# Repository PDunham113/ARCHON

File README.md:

# ARCHON
**A**ddressable **R**GB LED **CON**troller *(The **'h'** is nonexistent)*

The ultimate goal is to control an arbitrary number of addressable (WS2812 or
similar) from an ATMega328p, with a robust serial protocol to communicate to a
IoT-friendly mainboard (Raspberry Pi Zero W or similar).

Current state is somewhat less than that (setting up tools, etc.)

## Folders

### hardware (v0.0.0)
Contains EAGLE files for the ARCHON controller board

### software (v0.0.0)
Contains firmware for ARCHON

## Setup
Working with the hardware requires an installation of Autodesk EAGLE (v8.5.2 or
later), as well as a copy of Sparkfun's EAGLE library. Installation is left up
to the user.

Working with the software requires a number of (non-Windows-friendly) tools. To
automate the installation process and facilitate the ability to work on
multiple projects at once, a Vagrantfile is maintained with all the required
tools and dependencies.

### Installing Vagrant
You will need:
-   Vagrant [(HashiCorp)][vagrant_install]
-   VirtualBox [(Oracle)][virtualbox_install]
    -   Other VMs are available, but not actively supported by this project
-   VirtualBox Extensions [(Same place)][virtualbox_install]

The Vagrantfile used here is split into 3 parts.
-   `Vagrantfile`
    -   Deals with general configuration of VM instance
-   `Vagrantfile.project`
    -   Deals with project-specific tools and dependencies
-   `Vagrantfile.local`
    -   Deals with user preferences and machine-specific settings. As this is
        user-specific, Git will ignore this. A template
        (`Vagrantfile.local.example`) is included. Rename and enjoy!

To boot the VM, navigate to the project folder and run the following commands:
```
vagrant up
vagrant ssh
```

#### Common Errors
-   Ensure that virtualization extensions are enabled (you may need to check
    your BIOS)

[vagrant_install]: https://www.vagrantup.com/downloads.html
[virtualbox_install]: https://www.virtualbox.org/wiki/Downloads

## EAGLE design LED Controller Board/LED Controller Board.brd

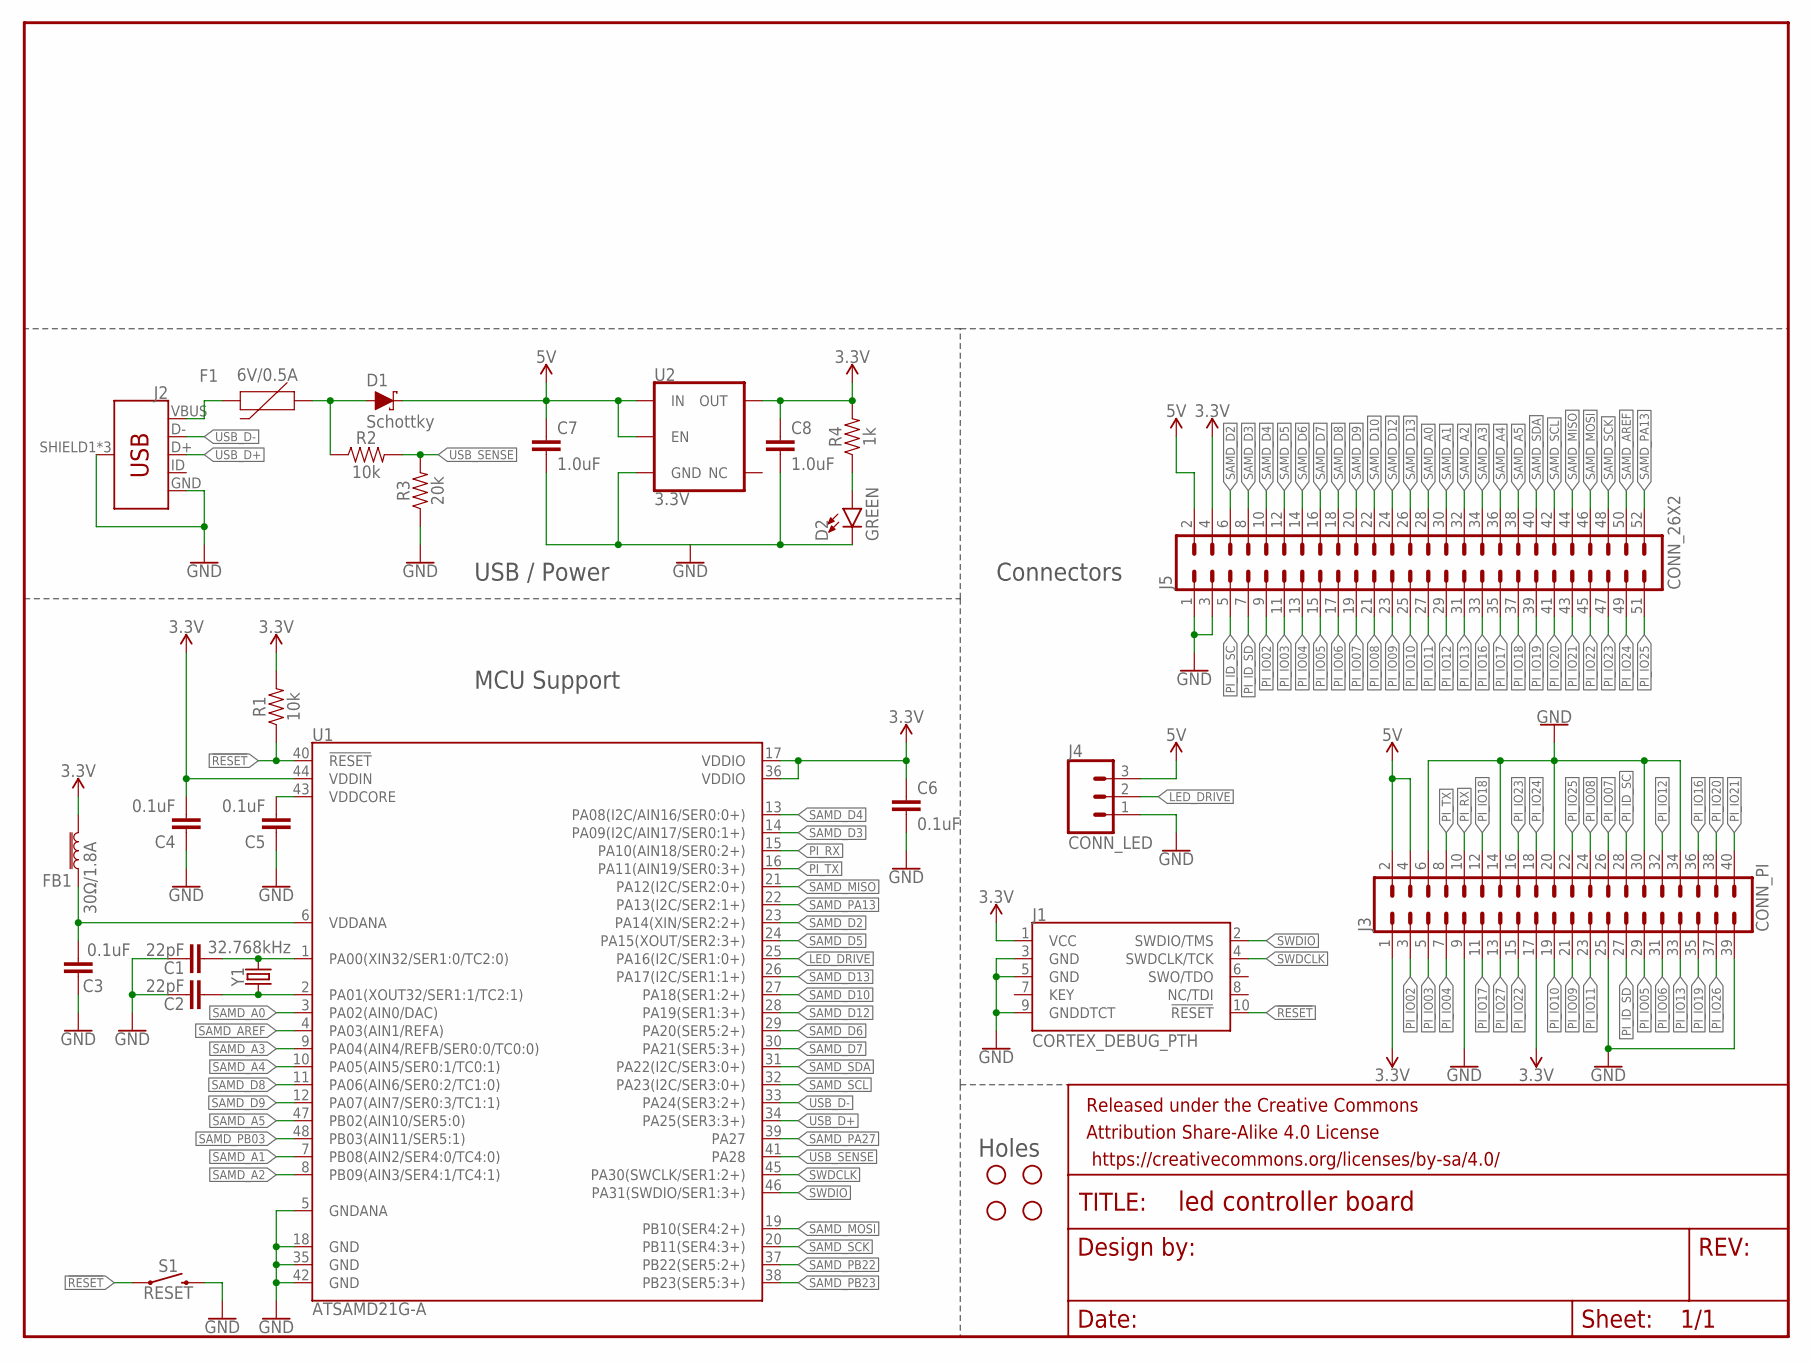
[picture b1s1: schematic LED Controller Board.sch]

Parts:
C1, C2: 22pF; 0603
C3, C4, C5, C6: 0.1uF; 0603
C7, C8: 1.0uF; 0603
D1: Schottky; SOD-323
D2: GREEN; LED-0603
F1: 6V/0.5A; 1206
FB1: 30Ω/1.8A; 0603
FRAME1: FRAME-LETTERNO_PACKAGE; DUMMY
H1, H2, H3, H4: STAND-OFFTIGHT; STAND-OFF-TIGHT
J1: CORTEX_DEBUG_PTH; 2X5-PTH-1.27MM
J2: USB_MICRO-B_FEMALE-SMT; USB-B-MICRO-SMD
J3: CONN_PI; 2X20
J4: CONN_LED; 1X03_LOCK
J5: CONN_26X2; 2X26
R1, R2: 10k; 0603
R3: 20k; 0603
R4: 1k; 0603
S1: RESET; TACTILE_SWITCH_PTH_RIGHT_ANGLE_KIT
U1: ATSAMD21G-A; TQFP-48
U2: 3.3V; SOT23-5
Y1: 32.768kHz; CRYSTAL-SMD-3.2X1.5MM

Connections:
3.3V: C4.2, C6.1, C8.1, FB1.2, J1.1 (VCC), J3.1, J3.17, J5.4, R1.2, R4.2, U1.17 (VDDIO), U1.36 (VDDIO), U1.44 (VDDIN), U2.5 (OUT)
5V: C7.1, D1.C, J3.2, J3.4, J4.3, J5.2, U2.1 (IN), U2.3 (EN)
!RESET: J1.10 (!RESET), R1.1, S1.1, U1.40 (!RESET!)
GND: C1.1, C2.1, C3.1, C4.1, C5.1, C6.2, C7.2, C8.2, D2.C, J1.3 (GND), J1.5 (GND), J1.9 (GNDDTCT), J2.GND, J2.SHIELD1 (SHIELD), J2.SHIELD2 (SHIELD), J2.SHIELD3 (SHIELD), J3.6, J3.9, J3.14, J3.20, J3.25, J3.30, J3.34, J3.39, J4.1, J5.1, J5.3, R3.1, S1.2, U1.5 (GNDANA), U1.18 (GND), U1.35 (GND), U1.42 (GND), U2.2 (GND)
LED_DRIVE: J4.2, U1.25 (PA16(I2C/SER1:0+))
unnamed: C1.2, U1.1 (PA00(XIN32/SER1:0/TC2:0)), Y1.P$2 (2)
unnamed: C2.2, U1.2 (PA01(XOUT32/SER1:1/TC2:1)), Y1.P$1 (1)
unnamed: C3.2, FB1.1, U1.6 (VDDANA)
unnamed: C5.2, U1.43 (VDDCORE)
unnamed: F1.2, J2.VBUS
unnamed: D1.A, F1.1, R2.1
unnamed: D2.A, R4.1
PI_ID_SC: J3.28, J5.5
PI_ID_SD: J3.27, J5.7
PI_IO02: J3.3, J5.9
PI_IO03: J3.5, J5.11
PI_IO04: J3.7, J5.13
PI_IO05: J3.29, J5.15
PI_IO06: J3.31, J5.17
PI_IO07: J3.26, J5.19
PI_IO08: J3.24, J5.21
PI_IO09: J3.21, J5.23
PI_IO10: J3.19, J5.25
PI_IO11: J3.23, J5.27
PI_IO12: J3.32, J5.29
PI_IO13: J3.33, J5.31
PI_IO16: J3.36, J5.33
PI_IO17: J3.11, J5.35
PI_IO18: J3.12, J5.37
PI_IO19: J3.35, J5.39
PI_IO20: J3.38, J5.41
PI_IO21: J3.40, J5.43
PI_IO22: J3.15, J5.45
PI_IO23: J3.16, J5.47
PI_IO24: J3.18, J5.49
PI_IO25: J3.22, J5.51
PI_IO26: J3.37
PI_IO27: J3.13
PI_RX: J3.10, U1.15 (PA10(AIN18/SER0:2+))
PI_TX: J3.8, U1.16 (PA11(AIN19/SER0:3+))
SAMD_A0: J5.28, U1.3 (PA02(AIN0/DAC))
SAMD_A1: J5.30, U1.7 (PB08(AIN2/SER4:0/TC4:0))
SAMD_A2: J5.32, U1.8 (PB09(AIN3/SER4:1/TC4:1))
SAMD_A3: J5.34, U1.9 (PA04(AIN4/REFB/SER0:0/TC0:0))
SAMD_A4: J5.36, U1.10 (PA05(AIN5/SER0:1/TC0:1))
SAMD_A5: J5.38, U1.47 (PB02(AIN10/SER5:0))
SAMD_AREF: J5.50, U1.4 (PA03(AIN1/REFA))
SAMD_D2: J5.6, U1.23 (PA14(XIN/SER2:2+))
SAMD_D3: J5.8, U1.14 (PA09(I2C/AIN17/SER0:1+))
SAMD_D4: J5.10, U1.13 (PA08(I2C/AIN16/SER0:0+))
SAMD_D5: J5.12, U1.24 (PA15(XOUT/SER2:3+))
SAMD_D6: J5.14, U1.29 (PA20(SER5:2+))
SAMD_D7: J5.16, U1.30 (PA21(SER5:3+))
SAMD_D8: J5.18, U1.11 (PA06(AIN6/SER0:2/TC1:0))
SAMD_D9: J5.20, U1.12 (PA07(AIN7/SER0:3/TC1:1))
SAMD_D10: J5.22, U1.27 (PA18(SER1:2+))
SAMD_D12: J5.24, U1.28 (PA19(SER1:3+))
SAMD_D13: J5.26, U1.26 (PA17(I2C/SER1:1+))
SAMD_MISO: J5.44, U1.21 (PA12(I2C/SER2:0+))
SAMD_MOSI: J5.46, U1.19 (PB10(SER4:2+))
SAMD_PA13: J5.52, U1.22 (PA13(I2C/SER2:1+))
SAMD_PA27: U1.39 (PA27)
SAMD_PB03: U1.48 (PB03(AIN11/SER5:1))
SAMD_PB22: U1.37 (PB22(SER5:2+))
SAMD_PB23: U1.38 (PB23(SER5:3+))
SAMD_SCK: J5.48, U1.20 (PB11(SER4:3+))
SAMD_SCL: J5.42, U1.32 (PA23(I2C/SER3:0+))
SAMD_SDA: J5.40, U1.31 (PA22(I2C/SER3:0+))
SWDCLK: J1.4 (SWDCLK/TCK), U1.45 (PA30(SWCLK/SER1:2+))
SWDIO: J1.2 (SWDIO/TMS), U1.46 (PA31(SWDIO/SER1:3+))
USB_D+: J2.D+, U1.34 (PA25(SER3:3+))
USB_D-: J2.D-, U1.33 (PA24(SER3:2+))
USB_SENSE: R2.2, R3.2, U1.41 (PA28)

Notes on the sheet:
MCU Support
Connectors
USB / Power
Holes

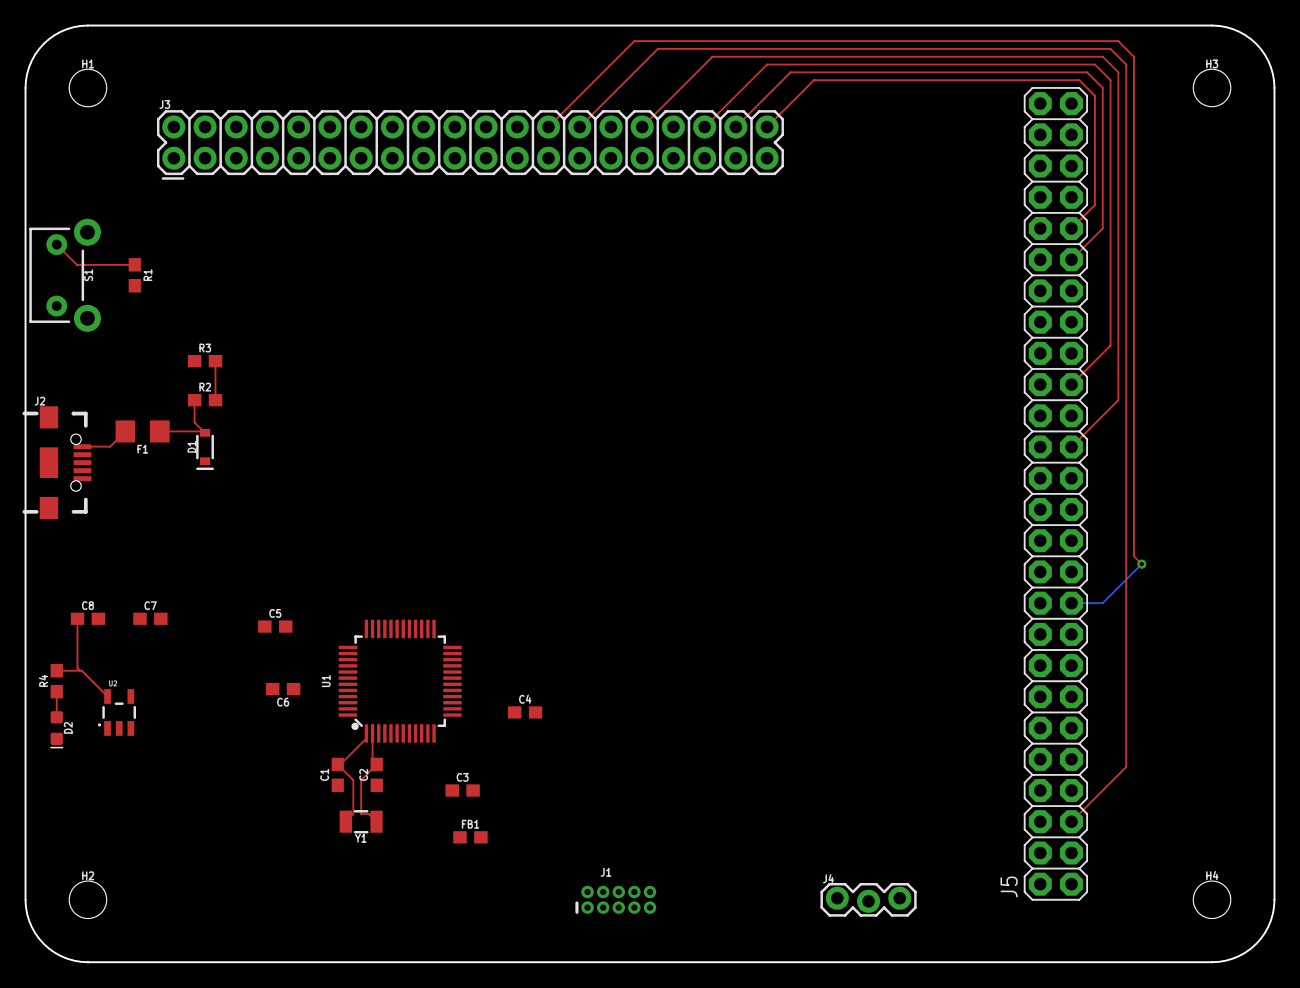
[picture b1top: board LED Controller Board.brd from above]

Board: 2 copper layers, 101.6 x 76.2 mm, 30 parts (0 on the bottom side), 67 nets.

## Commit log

2018-05-29 Add initial hardware layout
2018-05-29 Configure Vagrantfile
    Based on MITRE ectf Vagrant setup. Installs a number of tools used
    tocompile AVR C code, as well as Python
2018-06-15 Seperate into hardware/software, add comm library
2018-06-15 Restructure .gitignore
    Top-level & major subfolders each have their own file. Top-level
    currently ignores Vagrant crap; hardware ignored Eagle crap; software
    ignores software crap.
2018-06-15 Ignore Vagrant-generated log files, as well as GNU Make output
2018-06-15 Quick doc update
2018-06-15 Test communication library
2018-06-15 Update makefile with compiler optimzations
2018-06-15 Add initialization code, millis timer
2018-06-17 Better makefile
    Will automatically compile new .c files,
    nowproperlyrecompileswhenheaders change, and objects and binaries
    areplaced inseperatefoldersMakefile also has a configuration section
    forthe mostcommonchanges
2018-06-17 Refactor define blocks as enums, formatting standardization
2018-06-17 Fix comm config section
    Allow selection of "interrupt" function w/o delving into .c
2018-06-24 Create SPI module
2018-06-26 Create interface for RGB LEDs
2018-06-29 Move millis timer to module.
2018-06-29 Create RGB LED message protocol
2018-06-29 Add *some* lib version numbers. We'll see how it goes.
2018-07-07 Update Vagrantfile suite
2018-07-07 Initial draft of Python stuff
2018-09-11 Correctly handle start character constant
2018-09-12 Add basic support for color strings.

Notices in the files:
parts and their libraries:
SparkFun-Aesthetics: Licensing: Creative Commons ShareAlike 4.0 International - https://creativecommons.org/licenses/by-sa/4.0
SparkFun-Aesthetics: Released under the Creative Commons Attribution Share-Alike 4.0 License
SparkFun-Aesthetics: https://creativecommons.org/licenses/by-sa/4.0
